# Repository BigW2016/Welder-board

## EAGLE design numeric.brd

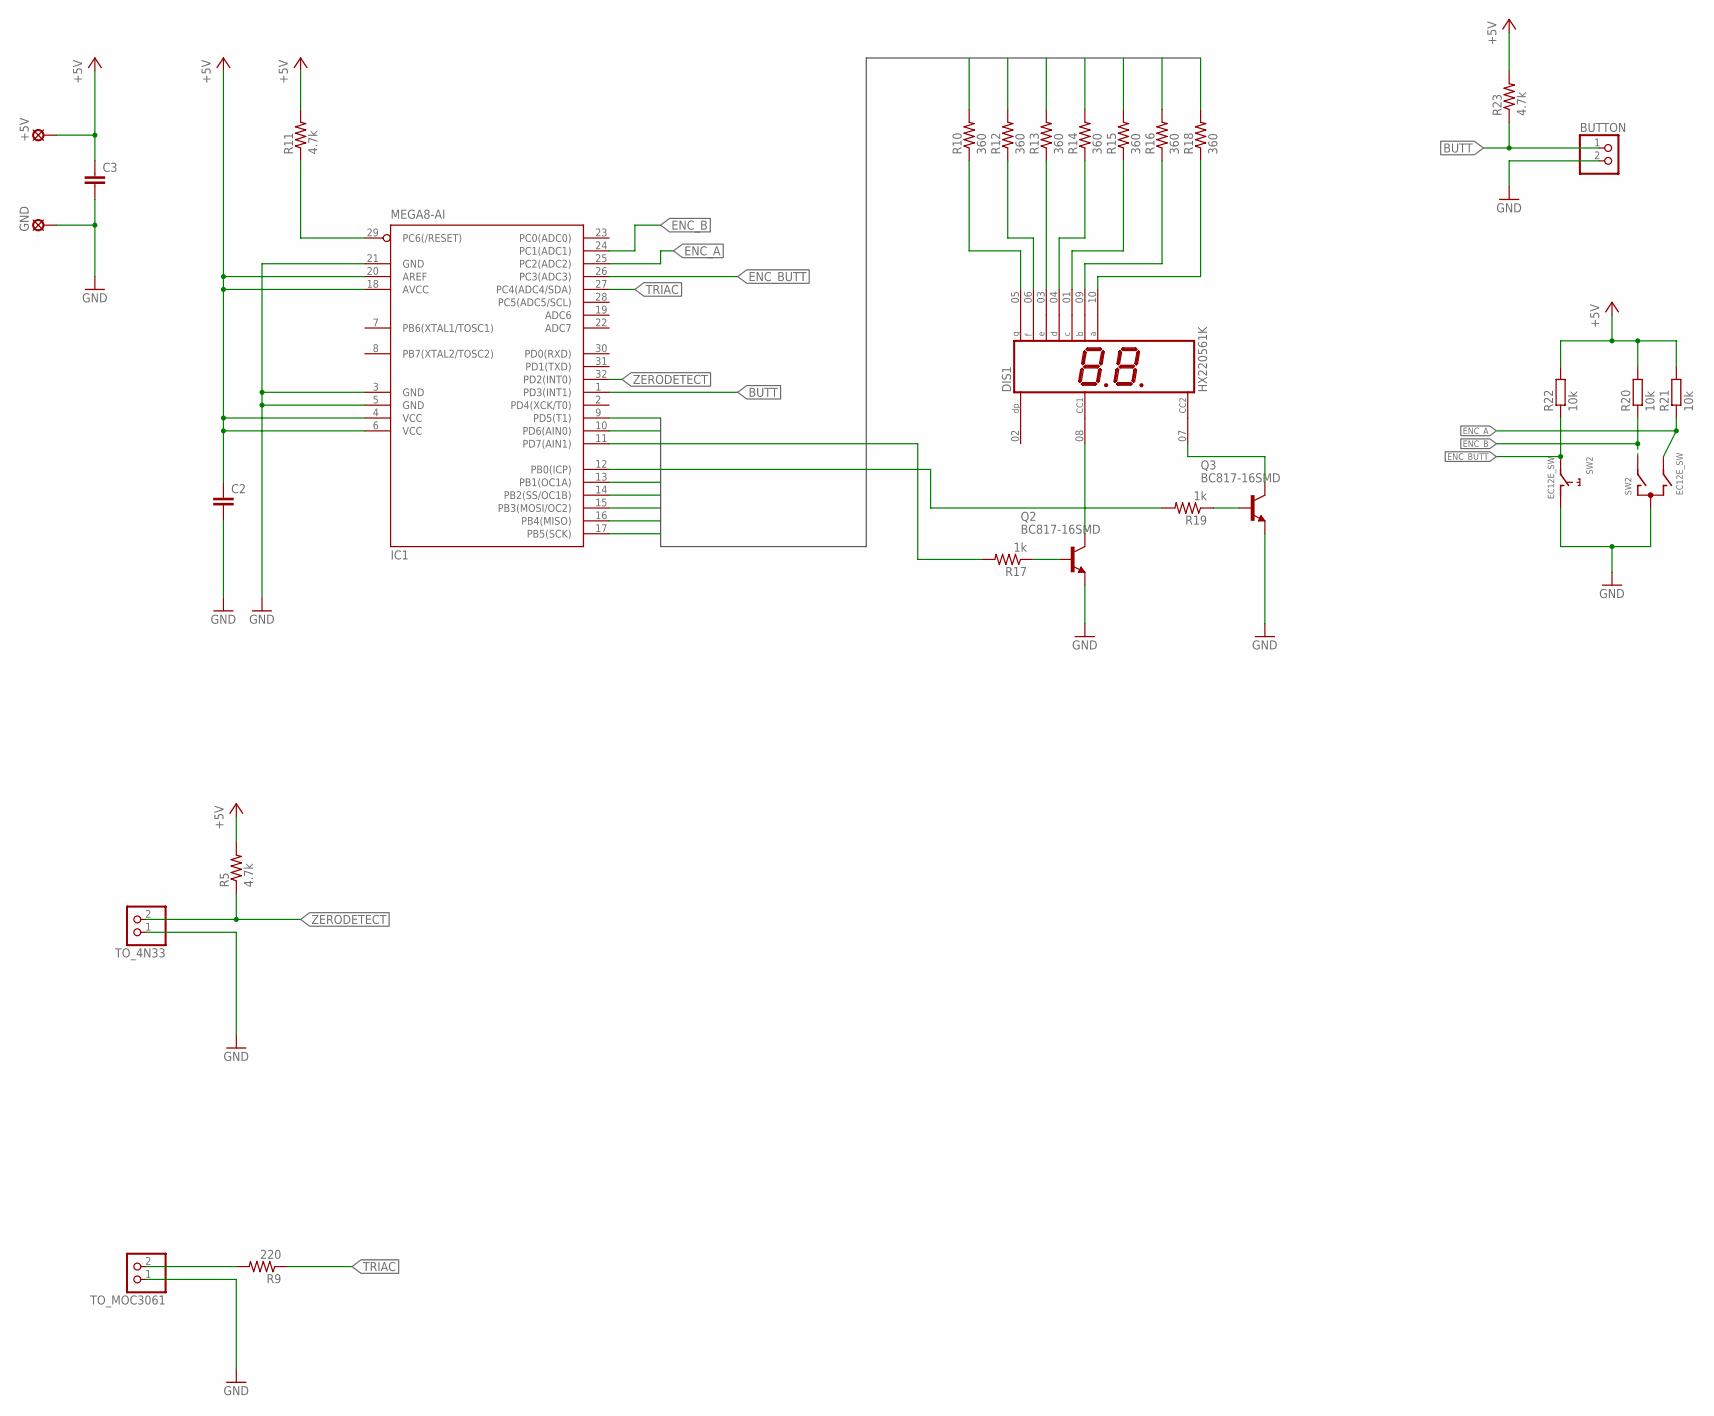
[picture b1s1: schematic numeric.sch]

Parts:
+5V: LSP10
BUTTON: PINHD-1X2; 1X02
C2, C3: C-EUC1206K; C1206K
DIS1: HX220561K
GND: LSP10
IC1: MEGA8-AI; TQFP32-08
Q2, Q3: BC817-16SMD; SOT23-BEC
R5, R11, R23: 4.7k; M1206
R9: 220; M1206
R10, R12, R13, R14, R15, R16, R18: 360; M1206
R17, R19: 1k; M1206
R20, R21, R22: 10k; R1206
SW2: EC12E_SW; ALPS_EC12E_SW
TO_4N33: PINHD-1X2; 1X02
TO_MOC3061: PINHD-1X2; 1X02

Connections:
+5V: +5V.MP, C2.1, C3.1, IC1.4 (VCC), IC1.6 (VCC), IC1.18 (AVCC), IC1.20 (AREF), R5.2, R11.2, R20.2, R21.2, R22.2, R23.2
B0: IC1.10 (PD6(AIN0)), R16.2
B1: IC1.9 (PD5(T1)), R18.2
B2: IC1.13 (PB1(OC1A)), R15.2
B3: IC1.14 (PB2(SS/OC1B)), R13.2
B4: IC1.15 (PB3(MOSI/OC2)), R14.2
B5: IC1.16 (PB4(MISO)), R10.2
B6: IC1.17 (PB5(SCK)), R12.2
BASE_Q2: IC1.11 (PD7(AIN1)), R17.2
BASE_Q3: IC1.12 (PB0(ICP)), R19.2
BUTT: BUTTON.1, IC1.1 (PD3(INT1)), R23.1
ENC_A: IC1.25 (PC2(ADC2)), R21.1, SW2.B
ENC_B: IC1.24 (PC1(ADC1)), R20.1, SW2.A
ENC_BUTT: IC1.26 (PC3(ADC3)), R22.1, SW2.E (BUTT)
GND: BUTTON.2, C2.2, C3.2, GND.MP, IC1.3 (GND), IC1.5 (GND), IC1.21 (GND), Q2.E, Q3.E, SW2.C, SW2.GND@1 (BUTT_GND), TO_4N33.1, TO_MOC3061.1
unnamed: DIS1.05 (G), R10.1
unnamed: DIS1.06 (F), R12.1
unnamed: DIS1.03 (E), R13.1
unnamed: DIS1.04 (D), R14.1
unnamed: DIS1.01 (C), R15.1
unnamed: DIS1.09 (B), R16.1
unnamed: DIS1.10 (A), R18.1
unnamed: DIS1.08 (CC1), Q2.C
unnamed: DIS1.07 (CC2), Q3.C
unnamed: Q3.B, R19.1
unnamed: Q2.B, R17.1
unnamed: R9.2, TO_MOC3061.2
RESET: IC1.29 (PC6(/RESET)), R11.1
TRIAC: IC1.27 (PC4(ADC4/SDA)), R9.1
ZERODETECT: IC1.32 (PD2(INT0)), R5.1, TO_4N33.2

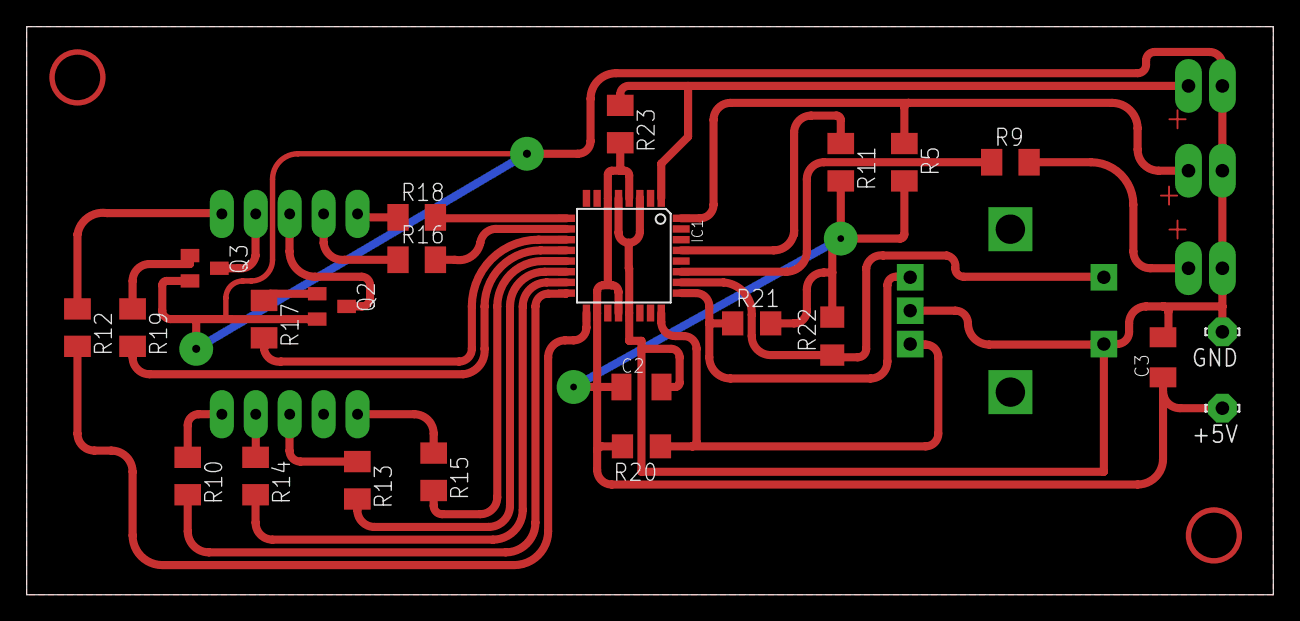
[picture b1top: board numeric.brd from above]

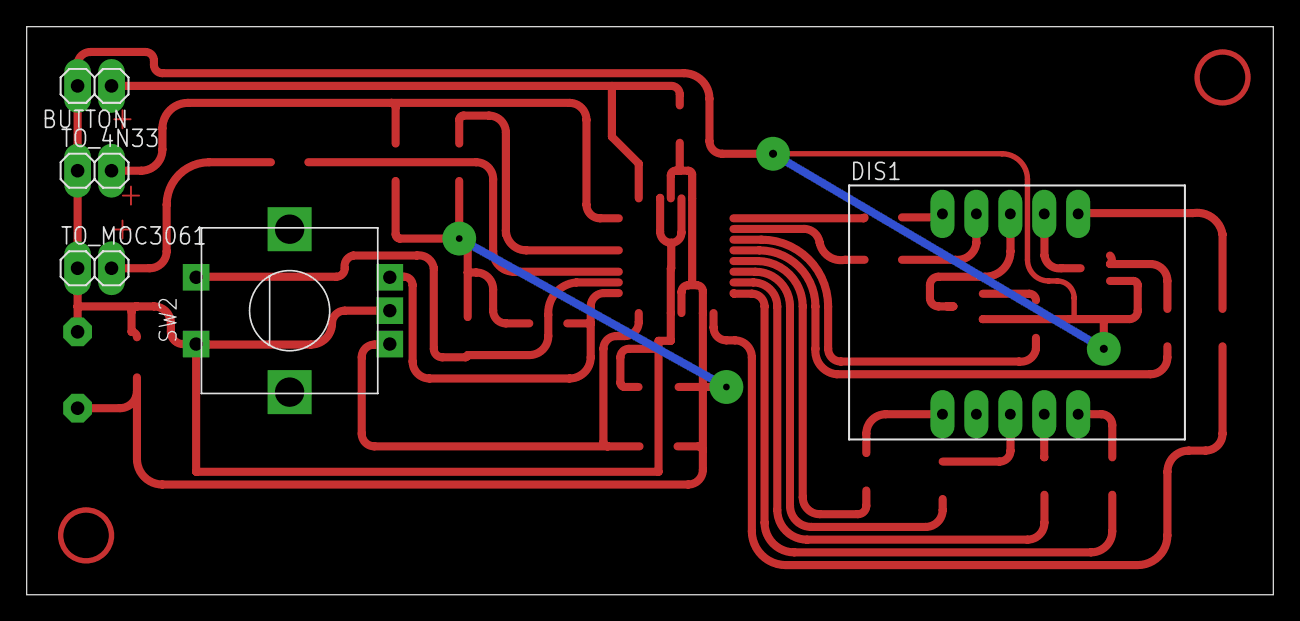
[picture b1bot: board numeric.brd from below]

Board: 2 copper layers, 93.3 x 42.5 mm, 28 parts (5 on the bottom side), 30 nets.

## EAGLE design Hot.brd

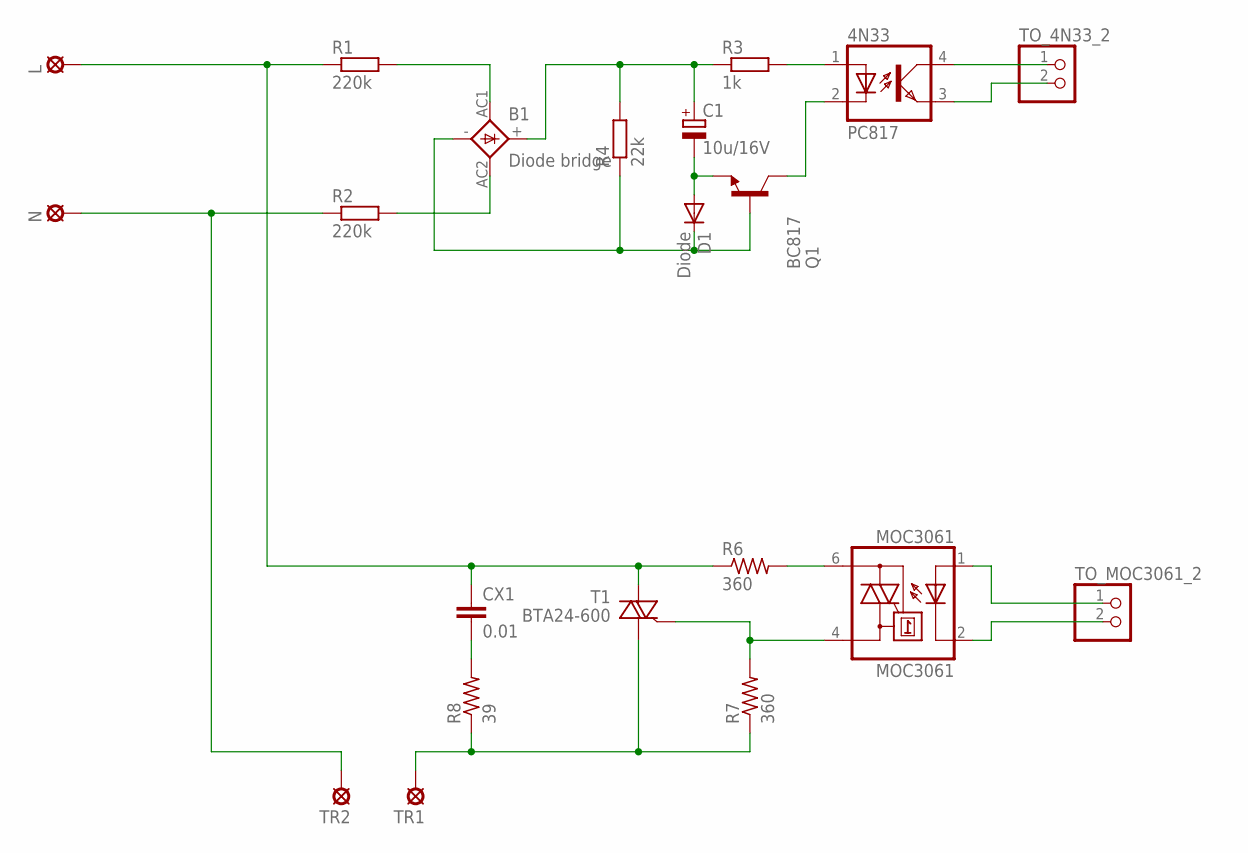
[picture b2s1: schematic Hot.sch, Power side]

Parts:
4N33: PC817; DIL04
B1: Diode bridge; 2KBB-R
C1: 10u/16V; E2,5-5
CX1: 0.01; XC10B6
D1: Diode; DO-214AC
L: LSP10
MOC3061: MOC3061; DIL06
N: LSP10
Q1: BC817; SOT23-BEC
R1, R2: 220k; M1206
R3: 1k; M1206
R4: 22k; M1206
R6, R7: 360; VTA54
R8: 39; VTA52
T1: BTA24-600; TO220DS
TO_4N33_2: PINHD-1X2; 1X02
TO_MOC3061_2: PINHD-1X2; 1X02
TR1, TR2: LSP10

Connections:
L: CX1.1, L.MP, R1.1, R6.1, T1.A2
N: N.MP, R2.1, TR2.MP
unnamed: 4N33.2 (C), Q1.C
unnamed: C1.-, D1.A, Q1.E
unnamed: 4N33.1 (A), R3.2
unnamed: B1.AC1, R1.2
unnamed: B1.-, D1.C, Q1.B, R4.1
unnamed: B1.+, C1.+, R3.1, R4.2
unnamed: B1.AC2, R2.2
unnamed: MOC3061.4 (A1), R7.2, T1.G
unnamed: MOC3061.6 (A2), R6.2
unnamed: CX1.2, R8.2
unnamed: R7.1, R8.1, T1.A1, TR1.MP
unnamed: 4N33.4 (COL), TO_4N33_2.1
unnamed: 4N33.3 (EMIT), TO_4N33_2.2
unnamed: MOC3061.2 (C), TO_MOC3061_2.2
TO_MOC3061: MOC3061.1 (A), TO_MOC3061_2.1

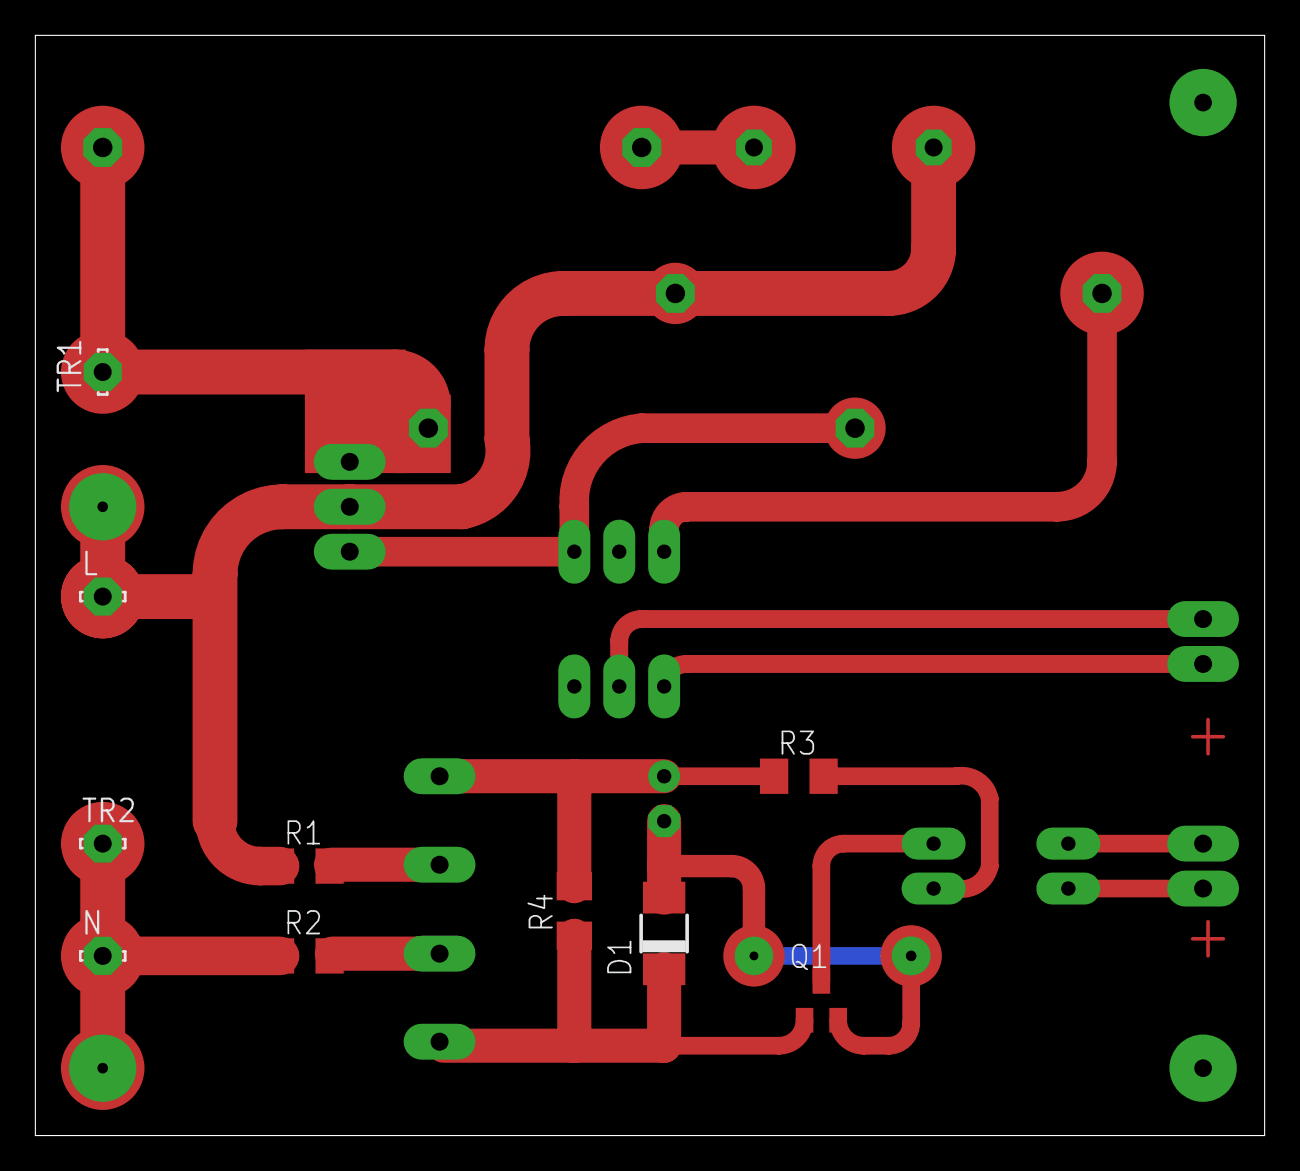
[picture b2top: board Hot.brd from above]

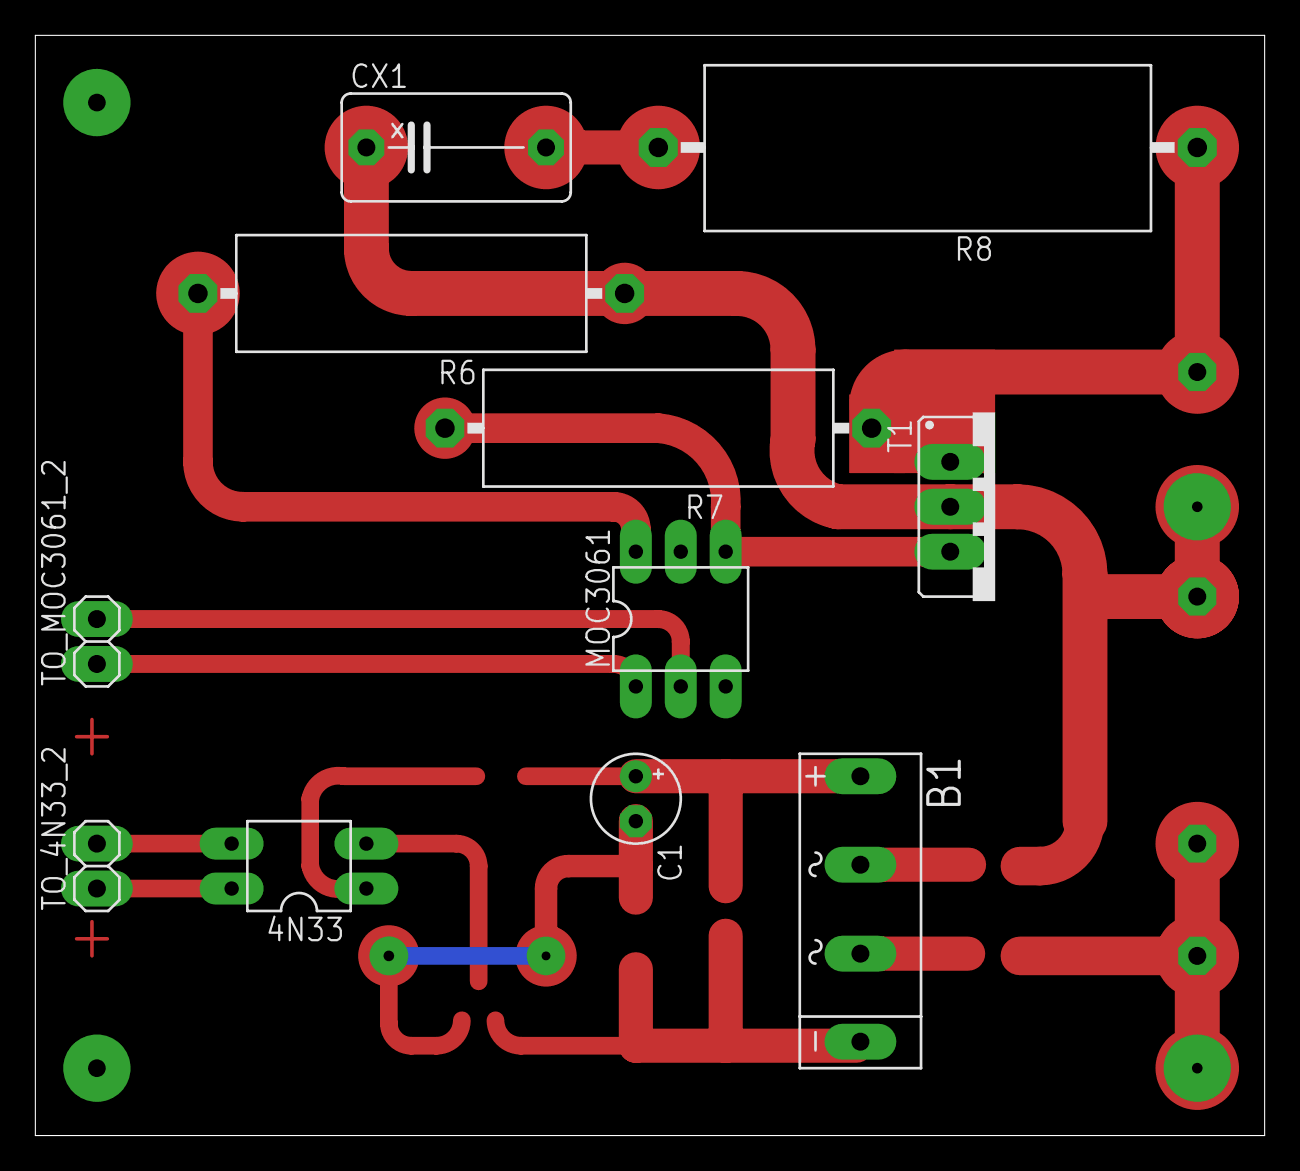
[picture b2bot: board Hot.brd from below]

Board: 2 copper layers, 69.5 x 62.2 mm, 21 parts (11 on the bottom side), 17 nets.

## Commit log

2017-11-27 вынес сварочник в отдельный репозиторий
2017-11-28 Добавил разводку на горизонтальную плату
2017-11-29 Провел проверку DRC
2017-11-29 Добавил отверстия для крепления платы
2017-12-02 чуть поправил - ничего существенного
2018-01-01 Переразвел 2горячую" плату - уменьшил длинну упарвляющей дорожки, увеличил ширину силовых дорожек. Под тиристором уменьшились зазоры - на перетрав, при необходимости - доработать напильником %) Добав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
2018-01-03 Маски в печать
